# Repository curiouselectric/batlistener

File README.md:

# Bat Listener
Design files for the Bat Listener kit as sold by https://www.curiouselectric.co.uk/

The kit is available to purchase here:
https://www.curiouselectric.co.uk/products/bat-listener-2016

This repository holds the design files for the PCB, the enclosure and the instructions

The PCB files have been designed using KiCAD (http://kicad.org/) which is open source, multiple platform and free to download.

The Enclosure design files have been produced using CorelDraw (a paid for program) but are aklso available as .dxf patterns for cutting on a laser cutter.

The instructions are available as an open-office document and as a .pdf for direct download.

Any comments or info please email: hello@curiouselectric.co.uk

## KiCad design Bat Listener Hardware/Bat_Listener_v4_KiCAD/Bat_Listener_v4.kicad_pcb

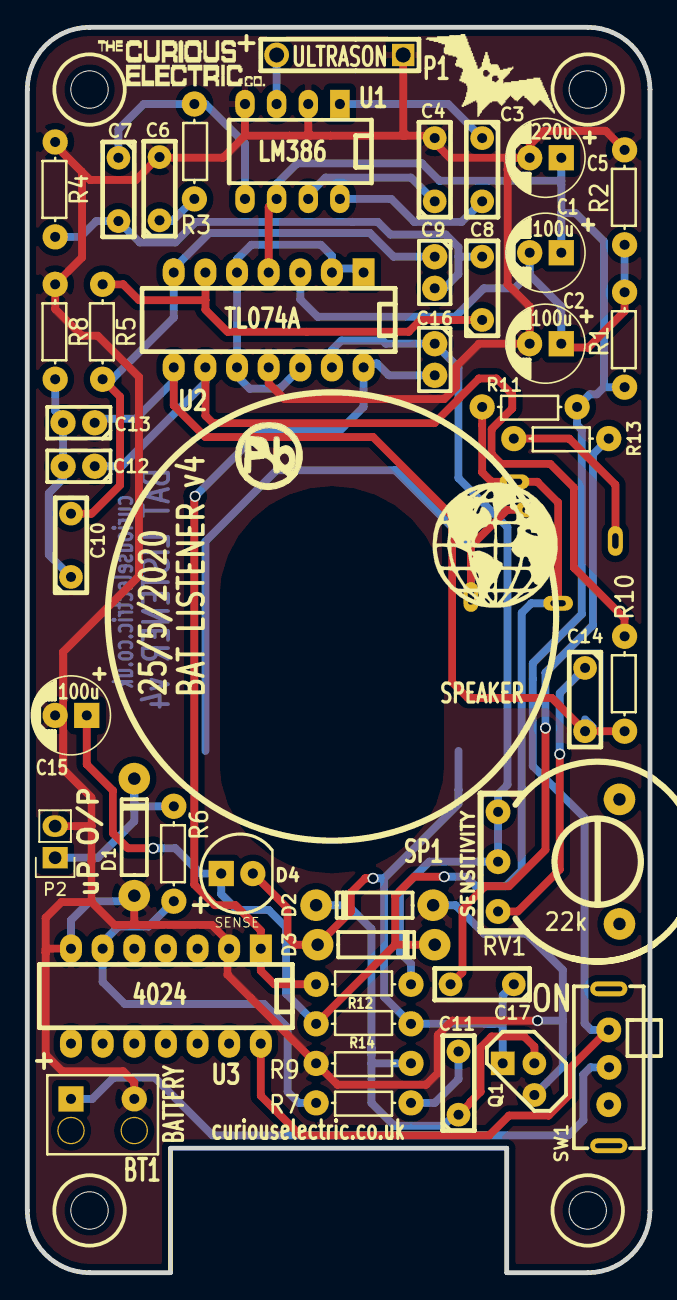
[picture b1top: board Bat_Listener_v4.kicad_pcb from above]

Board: 2 copper layers, 50.0 x 100.0 mm, 51 parts (1 on the bottom side), 29 nets.

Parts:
BT1: BATTERY; Batt_Connector_Strain_Relief
C1, C2, C15: 100u; C_1V7_TH
C3: 220n; C1_wide_lg_pad
C4, C6: 47n; C1_wide_lg_pad
C5: 220u; C_1V7_TH
C7: 2n2; C1_wide_lg_pad
C8: 1n5; C1_wide_lg_pad
C9, C16: 100p; C1_lg_pad
C10: 1n; C1_wide_lg_pad
C11, C17: 33n; C1_wide_lg_pad
C12, C13: 470p; C1_lg_pad
C14: 100n; C1_wide_lg_pad
D1: 5V1 ZENER; TH_Diode_1
D2, D3: 1N4148; TH_Diode_1
D4: SENSE; TH_LED-5MM
J1: PHONES; TH_3_5mm_Jack_oval_holes
P1: ULTRASON; TH_Ultra_sonic_Rx
P2: uP O/P; TH_Pin_Header_Straight_1x02
P3: NO_Pb; PH_LOGO_NO_Pb
P4: BAT; Bat_Logo
P5: PCB; PCB_50x100mm_PP3_CutOut
P10: LOGO1; TCEC_Words_13mm
P11: LOGO2; CuriousElectric_globe_10mm
Q1: BC337; NPN_BC337
R1, R2: 47k; TH_Resistor_1
R3: 10; TH_Resistor_1
R4: 1k3; TH_Resistor_1
R5: 150k; TH_Resistor_1
R6: 100k; TH_Resistor_1
R7, R8, R14: 1k; TH_Resistor_1
R9: 470k; TH_Resistor_1
R10: 560k; TH_Resistor_1
R11, R13: 100; TH_Resistor_1
R12: 10k; TH_Resistor_1
RV1: 22k; TH_PRESET_Thumb_Side
SP1: SPEAKER; TH_SPEAKER_36mm
SW1: ON/OFF; SW_SPDT_R_Angle_ALIEX
U1: LM386; DIP-8_300_ELL
U2: TL074A; DIP-14__300_ELL_lg_pad
U3: 4024; DIP-14__300_ELL_lg_pad

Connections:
+BATT: C1.1, C5.1, R1.1, R11.1, SW1.1, U1.6, U2.4, U3.14
GND: BT1.2, C2.2, C4.2, C5.2, C6.2, C15.2, D1.1, D2.1, P1.1, P2.2, Q1.3, R2.2, R4.2, R8.2, R9.2, U1.2, U1.4, U2.11, U3.2, U3.7
GNDA: U2.1, U2.2, U2.5, U2.10, U2.12
unnamed: BT1.1, SW1.2
unnamed: C1.2, C2.1, R1.2, R2.1, U2.3
unnamed: C3.1, U1.1
unnamed: C3.2, U1.8
unnamed: C4.1, U1.7
unnamed: C6.1, R3.2
unnamed: C7.1, R3.1, U1.5
unnamed: C7.2, C8.2, C9.2, R4.1
unnamed: C8.1, R5.2, U2.6
unnamed: C10.1, C12.2, C13.2, R8.1
unnamed: C9.1, C10.2, R5.1, U2.7
unnamed: C11.1, D2.2, Q1.2, R9.1
unnamed: C11.2, R7.1
unnamed: C12.1, R10.2, U2.9
unnamed: C13.1, C14.2, R10.1, U2.8
unnamed: C14.1, RV1.3
unnamed: C15.1, D3.2, D4.1, J1.2, J1.3, R11.2, R14.1
unnamed: C16.1, R12.2, RV1.1, RV1.2, U2.13
unnamed: C16.2, R12.1, U2.14, U3.1
unnamed: C17.1, D3.1, D4.2, Q1.1, R14.2, SP1.2
unnamed: C17.2, R13.1
unnamed: D1.2, P2.1, R6.2
unnamed: J1.1, R13.2
unnamed: J1.5, J1.6, SP1.1
unnamed: P1.2, U1.3
unnamed: R6.1, R7.2, U3.6

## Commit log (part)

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2015-11-30 Upload v2 design files
2015-12-03 Initial set of files
    2015 12 3
2017-01-10 Update to 2016 Bat Listener files
    Large change of all files to the new design
2017-01-10 Updated instructions
2017-02-17 First version - not correct!
2017-02-17 Changes 1
2017-02-17 Upload all instruction images
2017-09-05 Update of instructions
2017-09-10 new instructions in rst format
2017-09-10 Sorting instruction photos
2017-09-10 Added photo
2018-09-16 Updates Instructions
    A few changes for the new design case
2018-10-01 Update of instructions
    R6 changed
2020-05-25 Updated new PCB version
2020-08-08 Update of PCB and Enclosure Files
    Added headphone socket.
2020-09-14 Updated with headphone version
2020-11-21 Small changes to PCB and enclosure
2021-11-08 Update README.md
    https://forum.kicad.info/t/warning-avoid-all-links-to-kicad-pcb-org-use-kicad-org/31521
2021-11-12 Instruction update
2024-08-05 Updated enclosure design - added 3D model
2024-09-06 moved schematic.
2025-08-26 updated instructions - small change
